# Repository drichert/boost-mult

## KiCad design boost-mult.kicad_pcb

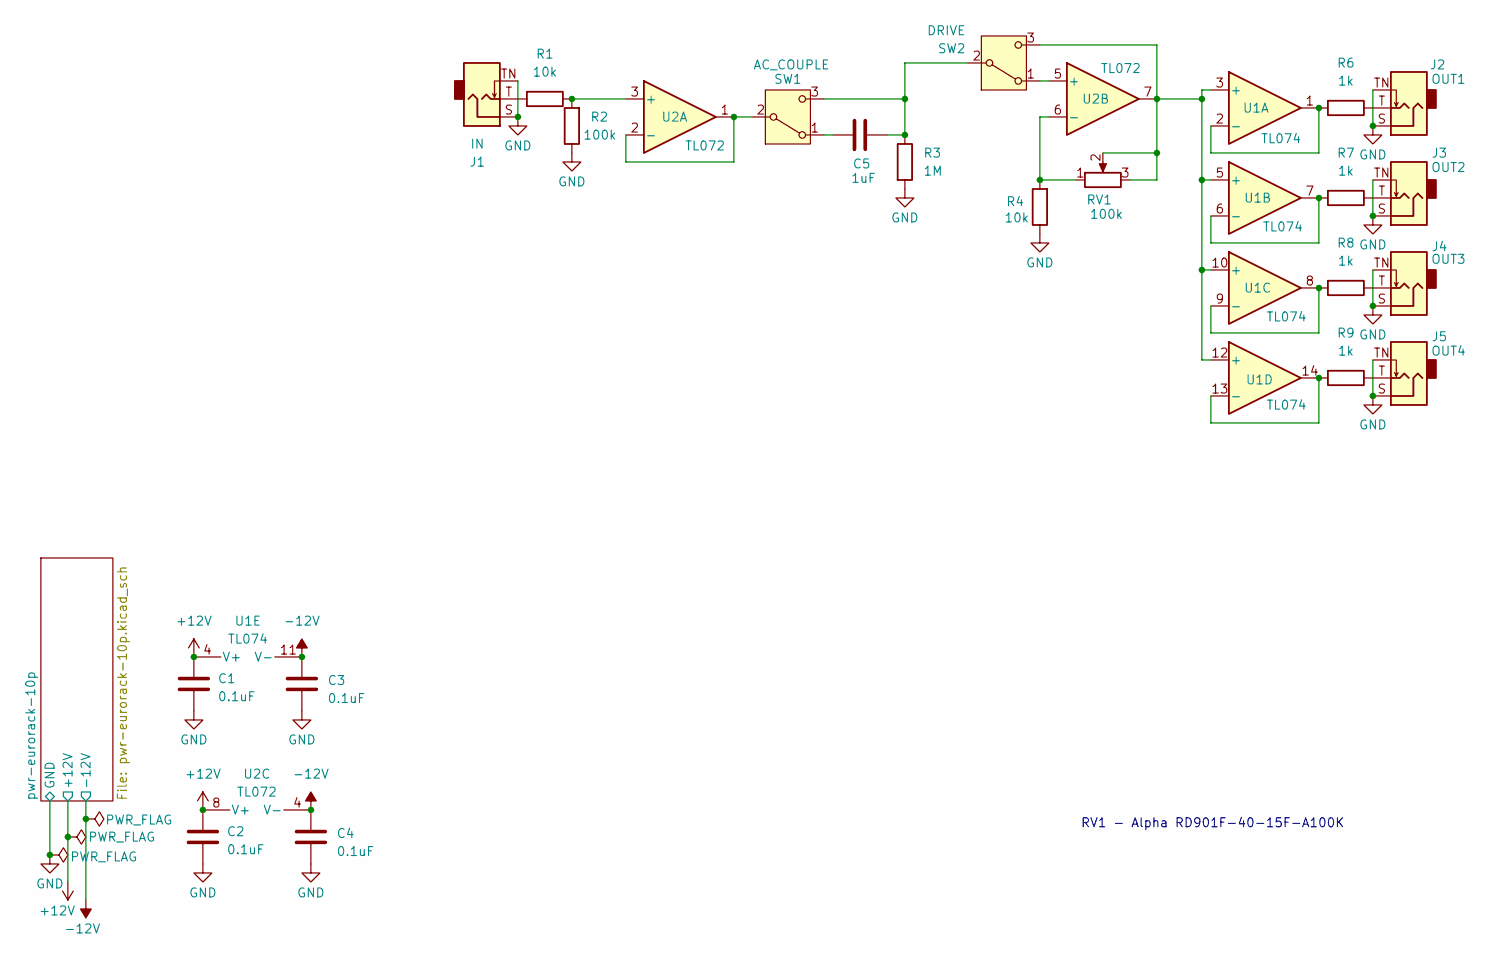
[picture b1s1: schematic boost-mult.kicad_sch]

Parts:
C1, C2, C3, C4: 0.1uF; C_0805_2012Metric
C5: 1uF; C_Rect_L7.2mm_W4.5mm_P5.00mm_FKS2_FKP2_MKS2_MKP2
J1: IN; Jack_3.5mm_QingPu_WQP-PJ398SM_Vertical_CircularHoles
J2: OUT1; Jack_3.5mm_QingPu_WQP-PJ398SM_Vertical_CircularHoles
J3: OUT2; Jack_3.5mm_QingPu_WQP-PJ398SM_Vertical_CircularHoles
J4: OUT3; Jack_3.5mm_QingPu_WQP-PJ398SM_Vertical_CircularHoles
J5: OUT4; Jack_3.5mm_QingPu_WQP-PJ398SM_Vertical_CircularHoles
R1, R4: 10k; R_0805_2012Metric
R2: 100k; R_0805_2012Metric
R3: 1M; R_0805_2012Metric
R6, R7, R8, R9: 1k; R_0805_2012Metric
RV1: 100k; Potentiometer_Alpha_RD901F-40-00D_Single_Vertical_CircularH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
SW1: AC_COUPLE; ToggleSwitch_1x03_P2.54mm_Vertical
SW2: DRIVE; ToggleSwitch_1x03_P2.54mm_Vertical
U1: TL074; SOIC-14_3.9x8.7mm_P1.27mm
U2: TL072; SOIC-8_3.9x4.9mm_P1.27mm

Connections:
+12V: C1.1, C2.1, U1.4 (V+), U2.8 (V+); also elsewhere on the board
-12V: C3.1, C4.1, U1.11 (V-), U2.4 (V-); also elsewhere on the board
GND: C1.2, C2.2, C3.2, C4.2, J1.S, J1.TN, J2.S, J2.TN, J3.S, J3.TN, J4.S, J4.TN, J5.S, J5.TN, R2.1, R3.2, R4.1; also elsewhere on the board
unnamed: J1.T, R1.2
unnamed: J2.T, R6.1
unnamed: J3.T, R7.1
unnamed: J4.T, R8.1
unnamed: J5.T, R9.1
unnamed: C5.1, SW1.1 (A)
unnamed: SW1.2 (B), U2.1, U2.2 (-)
unnamed: C5.2, R3.1, SW1.3 (C), SW2.2 (B)
unnamed: SW2.1 (A), U2.5 (+)
unnamed: RV1.2, RV1.3, SW2.3 (C), U1.3 (+), U1.5 (+), U1.10 (+), U1.12 (+), U2.7
unnamed: R6.2, U1.1, U1.2 (-)
unnamed: R7.2, U1.6 (-), U1.7
unnamed: R8.2, U1.8, U1.9 (-)
unnamed: R9.2, U1.13 (-), U1.14
unnamed: R1.1, R2.2, U2.3 (+)
unnamed: R4.2, RV1.1, U2.6 (-)

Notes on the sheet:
RV1 - Alpha RD901F-40-15F-A100K

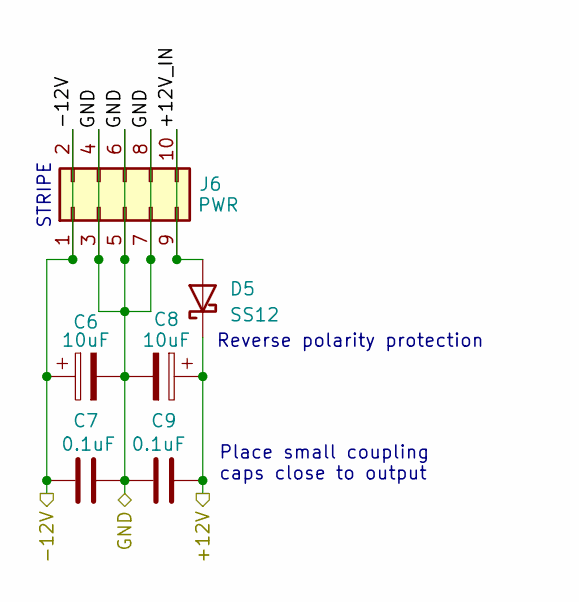
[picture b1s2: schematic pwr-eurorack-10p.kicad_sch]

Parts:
C6, C8: 10uF; CP_Radial_D5.0mm_P2.00mm
C7, C9: 0.1uF; C_0805_2012Metric
D5: SS12; D_SMA
J6: PWR; PinHeader_2x05_P2.54mm_Vertical

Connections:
+12V: C8.1, C9.2, D5.1 (K); also elsewhere on the board
-12V: C6.1, C7.1, J6.1, J6.2; also elsewhere on the board
/pwr-eurorack-10p/+12V_IN: D5.2 (A), J6.9, J6.10
GND: C6.2, C7.2, C8.2, C9.1, J6.3, J6.4, J6.5, J6.6, J6.7, J6.8; also elsewhere on the board

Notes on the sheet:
Reverse polarity protection
STRIPE
Place small coupling caps close to output

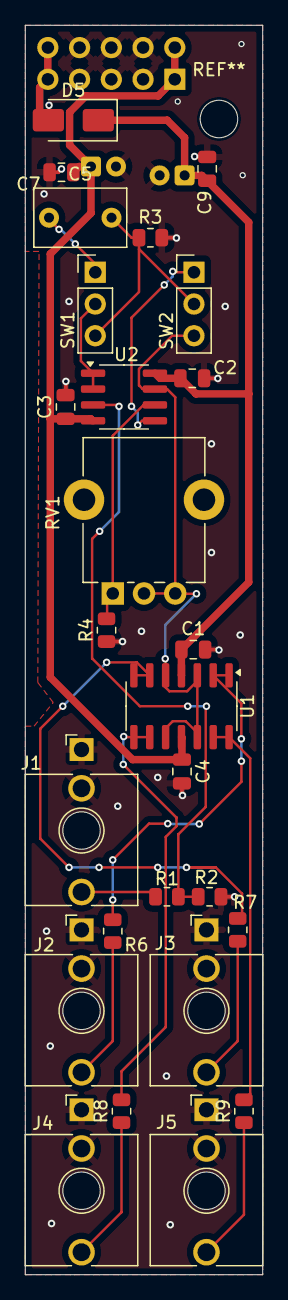
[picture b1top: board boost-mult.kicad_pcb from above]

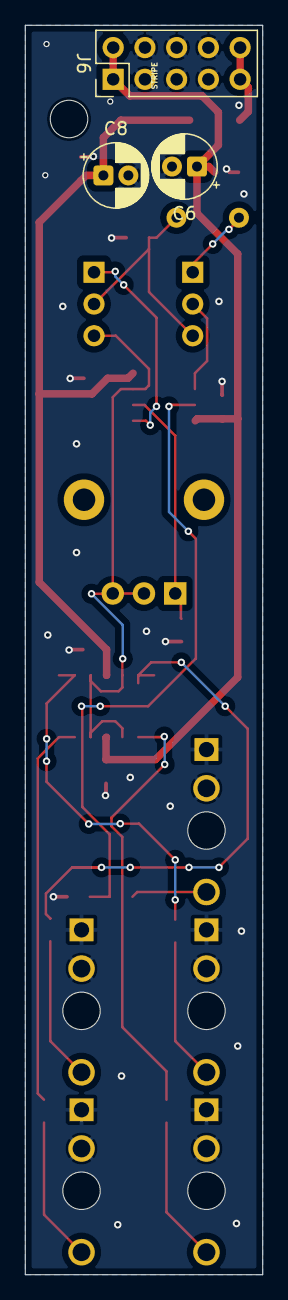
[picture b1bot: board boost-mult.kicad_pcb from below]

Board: 2 copper layers, 19.0 x 100.0 mm, 29 parts (3 on the bottom side), 20 nets.

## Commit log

2026-02-07 update switches
2026-02-08 jack layout, top layer gnd, vias
2026-02-08 save
2026-02-08 tweak top gnd pour
2026-02-08 wip mounting hole for standoff
2026-02-10 fixing DRC errors
2026-02-10 holes for panel, set origin for board
2026-02-10 holes
2026-02-11 tht film cap, move standoff hole
2026-02-14 fix incorrect power pin header
